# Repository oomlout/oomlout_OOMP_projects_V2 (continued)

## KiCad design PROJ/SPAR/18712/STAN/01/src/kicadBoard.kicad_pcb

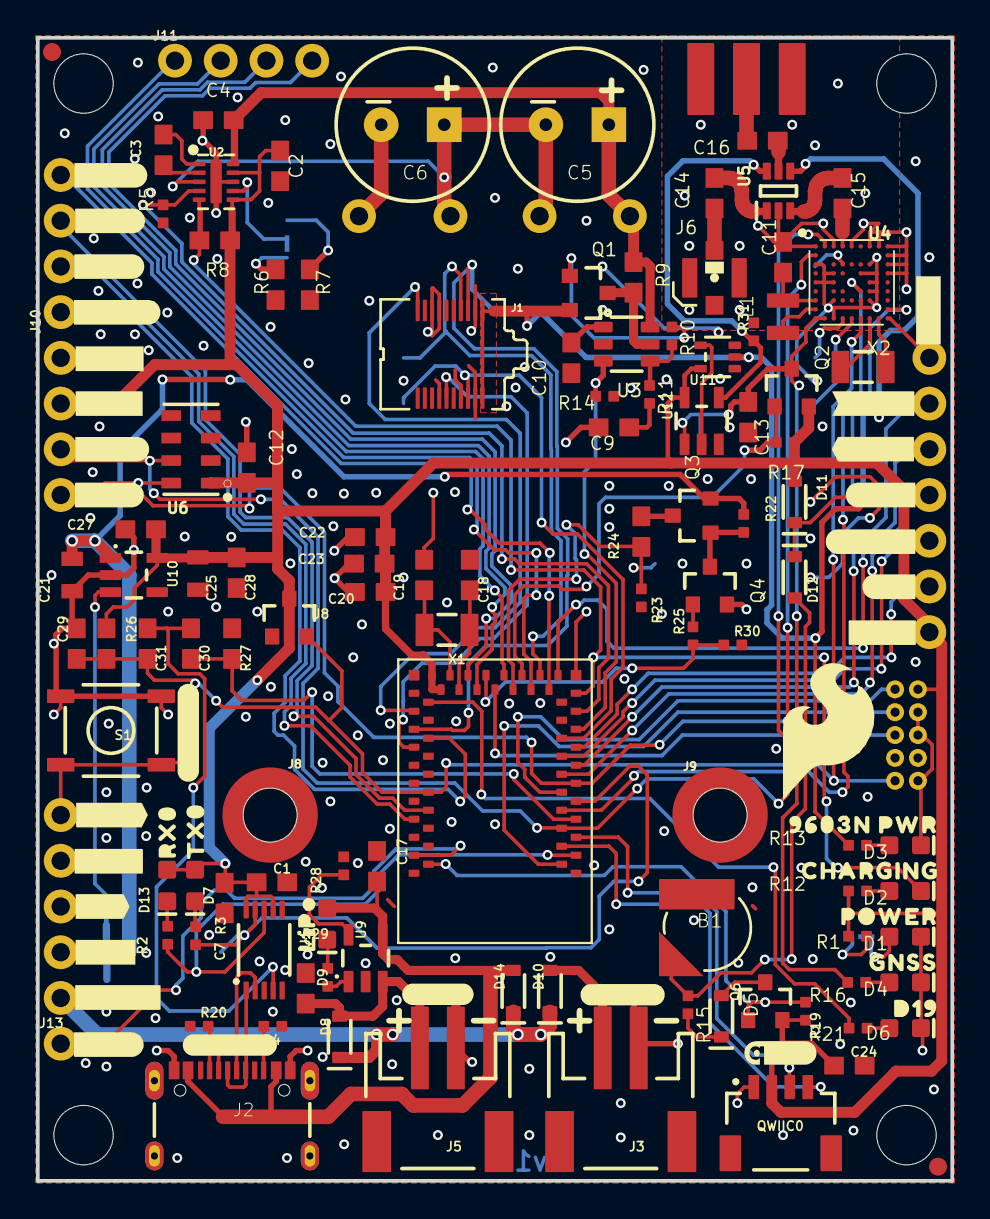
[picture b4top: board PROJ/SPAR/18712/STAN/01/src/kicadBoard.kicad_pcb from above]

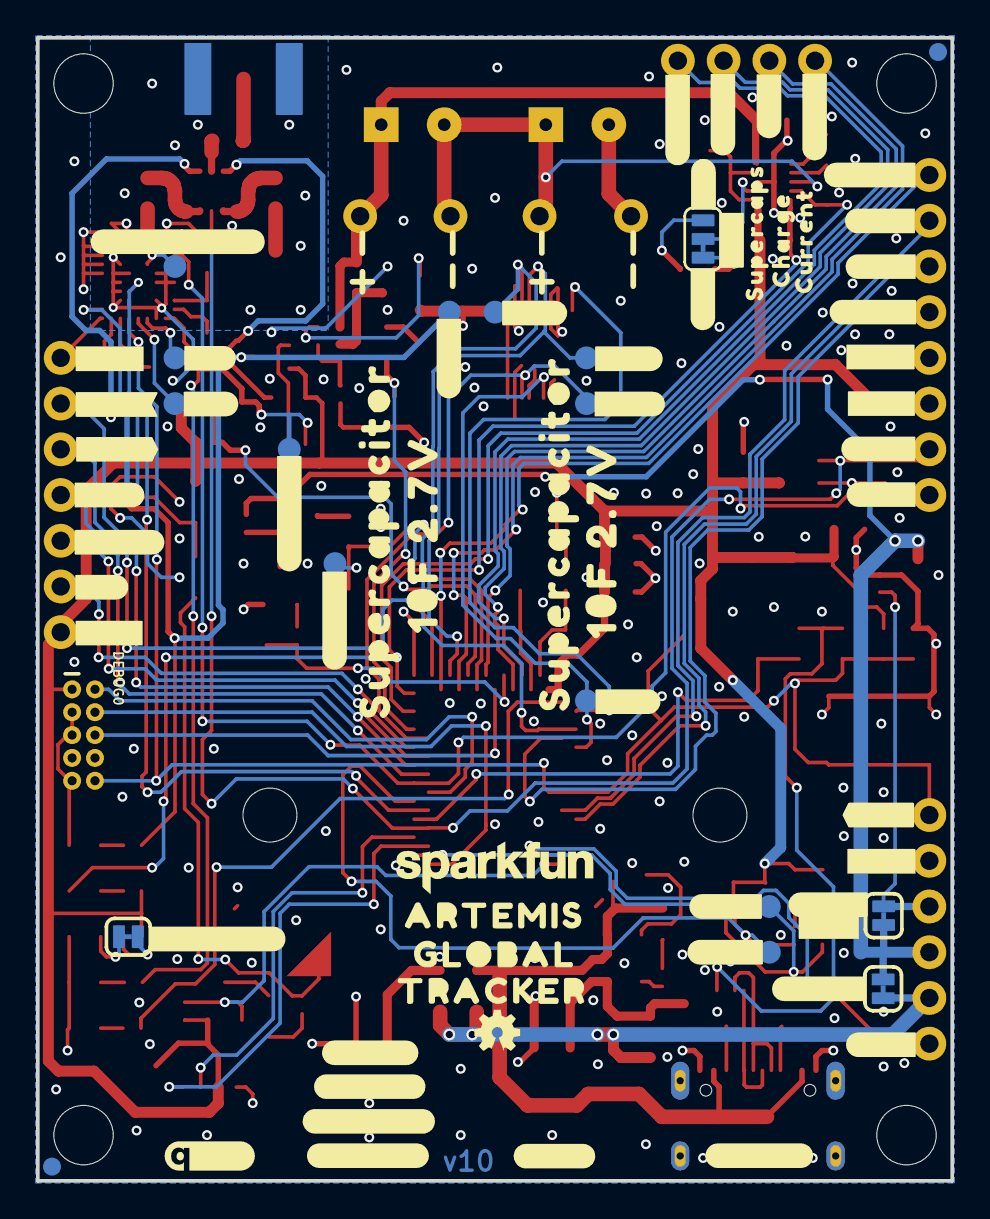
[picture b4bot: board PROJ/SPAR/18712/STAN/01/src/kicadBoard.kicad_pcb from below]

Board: 2 copper layers, 50.8 x 63.5 mm, 240 parts (79 on the bottom side), 101 nets.

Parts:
!RESET0: 1X01_NO_SILK
B1: ML414H_IV01E_BATTERY; ML414H_IV01E
C1, C9: 10nF; 0603
C2: 2.2uF; 0603
C3, C10, C23, C24, C27: 1.0uF; 0603
C4, C12: 0.22uF; 0603
C5, C6: 1F 2.7V; CPOL-RADIAL-1F-2.7V
C7, C13, C20, C28, C30, C31: 0.1uF; 0603
C8, C11, C17: 4.7uF; 0603
C14, C15, C16: 100pF; 0603
C18, C19: 15pF; 0603
C21, C25: 22uF; 0805
C22: 10uF; 0603
C29: 1nF; 0603
D1, D7: GREEN; LED-0603
D2, D9, D13: Yellow; LED-0603
D3: RED; LED-0603
D4: BLUE; LED-0603
D5, D8, D10, D11, D12, D14: 0.5A/40V/420mV; SOD-323
D6: WHITE; LED-0603
D17, D41: PAD.03X.05
DEBUG0: CORTEX_DEBUG; 2X5-PTH-1.27MM-NO_SILK
EN0: 1X01_NO_SILK
FRAME3: FRAME-LETTERNO_PACKAGE; DUMMY
FRAME5: FRAME-LEDGER; CREATIVE_COMMONS
GND0: 1X01_NO_SILK
GPS_RX0: TEST-POINT3X5; PAD.03X.05
GPS_TX0: TEST-POINT3X5; PAD.03X.05
I2C0: PTH; 1X04_NO_SILK
J1: IRIDIUM_9603N
J2: USB-C; USB-C-16P-2LAYER-PADS
J3, J5: JST-2-SMD
J4: 1X02_NO_SILK
J6: U.FL
J7: ANTENNA-GROUNDEDEDGE_SMA; SMA-EDGE
J8, J9: STAND-OFF-REFLOW-M2.0_6.0MM_TALL; STAND-OFF-REFLOW-M2.0
J10, J11: 1X04_NO_SILK
J13: 1X01_NO_SILK
JP1: JUMPER-SMT_3_1-NC_TRACE_SILK; SMT-JUMPER_3_1-NC_TRACE_SILK
JP2: JUMPER-SMT_2_NC_TRACE_SILK; SMT-JUMPER_2_NC_TRACE_SILK
JP7, JP8, JP13, JP14: FIDUCIAL1X2; FIDUCIAL-1X2
JP9, JP10, JP11, JP12: STAND-OFF
L1: 2.2uH; 0806
LOGO1: SFE_LOGO_NAME.1_INCH; SFE_LOGO_NAME_.1
LOGO2: SFE_LOGO_FLAME.3_INCH; SFE_LOGO_FLAME_.3
LOGO4: OSHW-LOGOMINI; OSHW-LOGO-MINI
MEAS0: JUMPER-SMT_2_NC_TRACE_SILK; SMT-JUMPER_2_NC_TRACE_SILK
Q1: 5.8A/30V/35mΩ; SOT23-3
Q2, Q3, Q6: 20V/4.2A/52mΩ/1.4W; SOT23-3
Q4: 600mA/40V; SOT23-3
QWIIC0: QWIIC_RA; JST04_1MM_RA
R1: 330; 0402-TIGHT
R2, R3, R12, R16, R21, R25, R29: 1k; 0402-TIGHT
R4, R20: 5.1k; 0402-TIGHT
R5, R14, R17, R19, R22, R23, R30: 10K; 0402-TIGHT
R6: 12k; 0603
R7: 30.1k; 0603
R8, R26: 100k; 0603
R9: 0.015ohm; 0603
R10, R11: 100; 0402-TIGHT
R13, R28: 2.0K; 0402-TIGHT
R15: 3.3K; 0402-TIGHT
R24: 20k; 0603
R27: 220k; 0603
R31: 20k; 0402-TIGHT
RX0, RX1: TEST-POINT3X5; PAD.03X.05
S1: RESET; TACTILE_SWITCH_SMD_5.2MM
SAFEBOOT0: TEST-POINT3X5; PAD.03X.05
SC1+0, SC1-0, SC2+0, SC2-0: 1X01_NO_SILK
SPI0: 1X07_NO_SILK
TX0, TX1: TEST-POINT3X5; PAD.03X.05
U1: CH340E_MSOP10; MSOP10
U2: LTC3225EDDB; DFN300X200-10L
U3: ADM4210_1TSOT6; TSOT6
U4: u-blox_ZOE_M8Q-0-10; UBLOX_ZOE_M8-0-10
U5: AS179-92LF; SOT65P220X100-6N
U6: MS8607-02BA01
U7: ARTEMIS_MODULESMD; ARTEMIS_FP
U8: V_SUPERVISOR_BD48K24G_2.4V; SOT23-3
U9: MCP73831; SOT23-5
U10: 3.3V; SOT23-5
U11: 74LVC1G04SE; SOT353
U12: 74LVC1G08W5-7; SOT23-5
U$1, U$13: SUPERCAPACITOR151
U$2: #SCK#199608
U$3, U$43: #3V3#0
U$4: #SDA#0
U$5: #USB#C#0
U$6: #SCL#0
U$7: #VIN#158
U$8: #3V3SW#0
U$9: CHARGING9604
U$10: #COPI#9694
U$11: QWIIC_4MM
U$12: LIPO5
U$14, U$15: 10F_2#7V152
U$16: RX06
U$17, U$70: #3V3#153
U$18: TX07
U$19: #AD35#199609
U$20, U$36: #GND#0
U$21: #SDA#153
U$22: #SCL#154
U$24: #AD31#7
U$25: QWIIC_5MM
U$26: #_RST##156
U$27: #EN#157
U$28: #VIN#3#0
U$29: #AD35#0
U$30: ARTEMIS0
U$31: SUPERCAPS6
U$32: #D17#0
U$33: #SAFEBOOT#0
U$34: #TX0#0
U$35: #TX1#0
U$37: #RX#0
U$38: #RX1#0
U$39: #TX#0
U$40: #5#3V#0
U$41: #D41#0
U$42: #RX0#0
U$44: #RESET#162
U$45: #SOLAR#165
U$46: #LIPO#164
U$47: #MEAS#0
U$48: #3V3_#0
U$50: #D4#36
U$51: GLOBAL0
U$52: TRACKER0
U$53: #LIPO#0
U$54: #_EN_#0
U$55: #SOLAR#0
U$56: #USB#C#161
U$57: #3_X_AA#0
U$58: #VBUS#159
U$59: #AD32#152
U$60: #SCK#9696
U$61: #PWR_LED#0
U$63: #D4#5
U$64: #CIPO#2
U$65: #3_X_AAA#0
U$66: #6V_MAX#0
U$67: CHARGE8
U$69: CURRENT9
U$71: #D42#32
U$72: #D37#152
U$73: #D43#43
U$74: #150#61
U$75: #COPI#5
U$76, U$77, U$78: #GND#152
U$79: #A32#44
U$80: #MA#45
U$81: #60#46
U$82: #D43#151
U$83: #D42#151
U$84: #AD31#151
U$85: #AD12#151
U$86: #D15#151
U$87: #AD11#151
U$88: #AD29#151
U$89: #CIPO#151
U$90: #D37#0
U$91: #GND#38
U$92: ##RST##39
U$93: 9603N_PWR40
U$94: POWER9605
U$95: GNSS9606
U$96: D199607
UNK3V3EN0: JUMPER-SMT_2_NC_TRACE_SILK; SMT-JUMPER_2_NC_TRACE_SILK
UNK3V3SW0: PAD.03X.05
UNK5V3: TEST-POINT3X5; PAD.03X.05
VIN/3: TEST-POINT3X5; PAD.03X.05
X1, X2: 32.768kHz; CRYSTAL-SMD-3.2X1.5MM

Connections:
3.3V: C1.1, C2.1, C7.1, C12.1, C20.2, C22.1, C23.1, C24.1, C25.1, C27.1, C28.1, D7.A, D11.A, D13.A, DEBUG0.1, I2C0.2, Q2.2, Q6.2, QWIIC0.2, R1.2, R8.2, R12.2, R17.2, R19.2, R26.2, SPI0.7, U1.7, U1.10, U2.6, U2.9, U6.1, U7.VDD@36, U7.VDD@37, U8.3, U10.5, U11.5, U12.5
3V3SW: C13.1, Q2.3, R16.2, U4.24, U4.25, U12.1, UNK3V3SW0.1
ANTENNA: C16.1, J7.SIG
ARTEMIS_AD11: J11.3, U7.~AD11
ARTEMIS_AD12: J11.1, U7.~AD12
ARTEMIS_AD29: J11.4, U7.~AD29
ARTEMIS_AD31: J10.1, U7.~AD31
ARTEMIS_AD32: J10.4, U7.~AD32
ARTEMIS_BOOT: C30.2, R27.2, U7.BOOT
ARTEMIS_D4: SPI0.6, U7.~D4
ARTEMIS_D5_SCK: SPI0.4, U7.~D5
ARTEMIS_D6_MISO: SPI0.3, U7.~D6
ARTEMIS_D7_MOSI: SPI0.2, U7.D7
ARTEMIS_D8_SCL: I2C0.4, U4.32, U6.8, U7.D8
ARTEMIS_D9_SDA: I2C0.3, U4.2, U6.7, U7.D9
ARTEMIS_D10: U4.50, U7.D10
ARTEMIS_D13: R23.1, R24.2, U7.~AD13, VIN/3.1
ARTEMIS_D15: J11.2, U7.D15
ARTEMIS_D17: D17.1, J1.5, U7.D17
ARTEMIS_D18: J1.19, U7.~D18
ARTEMIS_D19: R21.2, U7.~D19
ARTEMIS_D22: R14.1, U3.3, U7.~D22
ARTEMIS_D24: J1.6, TX1.1, U7.~D24
ARTEMIS_D25: J1.7, RX1.1, U7.~D25
ARTEMIS_D26: Q2.1, R17.1, U7.~D26
ARTEMIS_D27: R5.2, U2.4, U7.~D27
ARTEMIS_D28: D2.C, R8.1, U2.5, U7.~D28
ARTEMIS_D33: DEBUG0.6, U7.~AD33/SWO
ARTEMIS_D34: R25.1, R30.1, U7.AD34
ARTEMIS_D35: SPI0.5, U7.~AD35
ARTEMIS_D37: J13.1, U7.~D37
ARTEMIS_D39_SCL4: QWIIC0.4, U7.~D39
ARTEMIS_D40_SDA4: QWIIC0.3, U7.D40
ARTEMIS_D41: D41.1, J1.12, U7.D41
ARTEMIS_D42: J10.2, U7.~D42
ARTEMIS_D43: J10.3, U7.~D43
ARTEMIS_D44: Q6.1, R19.1, U7.~D44
ARTEMIS_RX0: R2.1, RX0.1, U1.8, U7.RXI-0
ARTEMIS_SWDCK: DEBUG0.4, U7.SWDCK
ARTEMIS_SWDIO: DEBUG0.2, U7.SWDIO
ARTEMIS_TX0: R3.1, TX0.1, U1.9, U7.TXO-0
ARTEMIS_~RESET: !RESET0.1, C29.1, C31.2, DEBUG0.10, R26.1, S1.3, S1.4, U4.20, U7.~RST, U8.2
ARTEMIS_~RTS: C30.1, C31.1, U1.4
CC3: J2.B5, R4.2
CC4: J2.A5, R20.2
D+2: J2.A6, J2.B6, U1.1
D-2: J2.A7, J2.B7, U1.2
EXT_PWR: J1.1, J1.2, Q1.2, R13.2, U5.4, U11.2, UNK5V3.1
GND: B1.-, C1.2, C2.2, C4.2, C6.-, C7.2, C8.2, C9.2, C10.2, C11.2, C12.2, C13.2, C17.2, C18.1, C19.1, C20.1, C21.2, C22.2, C23.2, C24.2, C25.2, C27.2, C28.2, C29.2, D1.C, D3.C, D4.C, D6.C, DEBUG0.3, DEBUG0.5, DEBUG0.9, GND0.1, I2C0.1, J1.3, J1.4, J1.8, J1.13, J1.14, J1.15, J1.18, J2.GND, J2.GND2, J3.1, J5.1, J6.1, J6.2, J7.GND@0, J7.GND@1, J7.GND@2, J7.GND@3, J8.1, J9.1, Q4.2, QWIIC0.1, R4.1, R5.1, R6.1, R7.2, R14.2, R20.1, R23.2, R27.1, R28.1, R30.2, R31.2, S1.1, S1.2, SC2-0.1, SPI0.1, U1.3, U2.8, U2.11, U3.2, U4.1, U4.3, U4.5, U4.7, U4.8, U4.9, U4.10, U4.11, U4.12, U4.17, U4.23, U4.29, U4.31, U4.37, U4.38, U4.39, U4.40, U4.41, U4.44, U4.46, U4.47, U4.49, U5.2, U6.3, U7.GND@1, U7.GND@22, U7.GND@38, U7.GND@39, U7.GND@47, U7.GND@59, U8.1, U9.2, U10.2, U11.3, U12.3
GNSS: C15.2, U4.4
IRIDIUM: C14.2, J6.FEED
LTC3225_VOUT: C4.1, C5.+, R9.2, SC1+0.1, U2.10, U3.6
unnamed: C5.-, C6.+, SC1-0.1, SC2+0.1, U2.3
unnamed: JP1.3, R6.2
unnamed: JP2.2, R1.1
unnamed: JP1.1, R7.1
unnamed: D2.A, R12.1
unnamed: D3.A, R13.1
unnamed: D5.A, Q6.3
unnamed: Q1.3, R9.1, U3.5
unnamed: C3.2, U2.2
unnamed: C3.1, U2.1
unnamed: JP1.2, U2.7
unnamed: Q1.1, R10.1
unnamed: R10.2, R11.1, U3.4
unnamed: C9.1, R11.2
unnamed: C10.1, U3.1
unnamed: L1.2, U4.26
unnamed: C11.1, L1.1, U4.27
unnamed: U4.18, X2.P$2
unnamed: U4.19, X2.P$1
unnamed: D5.C, R15.2
unnamed: D4.A, R16.1
unnamed: D13.C, R2.2
unnamed: D1.A, JP2.1
unnamed: D11.C, D12.C, U4.16
unnamed: SAFEBOOT0.1, U4.34
unnamed: GPS_RX0.1, U4.22
unnamed: GPS_TX0.1, U4.21
unnamed: C14.1, U5.1
unnamed: C15.1, U5.3
unnamed: C16.2, U5.5
unnamed: R31.1, U5.6, U12.4
unnamed: D7.C, R3.2
unnamed: U11.4, U12.2
unnamed: D6.A, R21.1
unnamed: EN0.1, U10.3, UNK3V3EN0.2
unnamed: Q3.1, Q4.3, R22.1
unnamed: R28.2, U9.5
unnamed: D9.C, R29.2
unnamed: R29.1, U9.1
unnamed: Q3.3, R24.1
unnamed: Q4.1, R25.2
VBUS: D8.C, D10.C, D14.C, J4.2, MEAS0.1
VIN: C21.1, J4.1, MEAS0.2, Q3.2, R22.2, U10.1, UNK3V3EN0.1
V_AAA: D10.A, J3.2
V_BATT: C8.1, D8.A, J5.2, U9.3
V_BCKP: B1.+, D12.A, R15.1
V_USB: C17.1, D9.A, D14.A, J2.VBUS1, J2.VBUS2, U9.4
XTALI: C19.2, U7.XI, X1.P$1
XTALO: C18.2, U7.XO, X1.P$2

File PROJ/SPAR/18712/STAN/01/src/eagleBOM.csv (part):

"Part";"Value";"Device";"Package";"Description";"DESIGNER";"PROD_ID";"REV";"SF_ID";"VALUE";"VERSION";"VOLTAGE";
"!RESET";"";"CONN_01PTH_NO_SILK_YES_STOP";"1X01_NO_SILK";"Single connection point. Often used as Generic Header-pin footprint for 0.1 inch spaced/style header connections";"";"";"";"";"";"";"";
"3V3EN";"JUMPER-SMT_2_NC_TRACE_SILK";"JUMPER-SMT_2_NC_TRACE_SILK";"SMT-JUMPER_2_NC_TRACE_SILK";"Normally closed trace jumper";"";"";"";"";"";"";"";
"3V3SW";"";"TEST-POINT3X5";"PAD.03X.05";"SparkFun Test Points";"";"";"";"";"";"";"";
"5V3";"TEST-POINT3X5";"TEST-POINT3X5";"PAD.03X.05";"SparkFun Test Points";"";"";"";"";"";"";"";
"B1";"ML414H_IV01E_BATTERY";"ML414H_IV01E_BATTERY";"ML414H_IV01E";"SEIKO ML414H-IV01E Reflowable Lithium Battery";"";"BATT-14267";"";"";"";"";"";
"C1";"10nF";"10NF-0603-50V-10%";"0603";"0.01uF/10nF/10,000pF ceramic capacitors";"";"CAP-00867";"";"";"10nF";"";"";
"C2";"2.2uF";"2.2UF-0603-10V-20%";"0603";"2.2µF ceramic capacitors";"";"CAP-07888";"";"";"2.2uF";"";"";
"C3";"1.0uF";"1.0UF-0603-16V-10%-X7R";"0603";"1µF ceramic capacitors";"";"CAP-13930";"";"";"1.0uF";"";"";
"C4";"0.22uF";"0.22UF-0603-25V-10%";"0603";"0.22µF ceramic capacitors";"";"CAP-07822";"";"";"0.22uF";"";"";
"C5";"1F 2.7V";"1F-2.7V(PTH)CPOL-RADIAL-1H-2.7V";"CPOL-RADIAL-1F-2.7V";"1F 2.7V SuperCapacitor CAP-14696";"";"CAP-14696";"";"";"";"";"";
"C6";"1F 2.7V";"1F-2.7V(PTH)CPOL-RADIAL-1H-2.7V";"CPOL-RADIAL-1F-2.7V";"1F 2.7V SuperCapacitor CAP-14696";"";"CAP-14696";"";"";"";"";"";
"C7";"0.1uF";"0.1UF-0603-25V-5%";"0603";"0.1µF ceramic capacitors";"";"CAP-08604";"";"";"0.1uF";"";"";
"C8";"4.7uF";"4.7UF-0603-6.3V-(10%)";"0603";"4.7µF ceramic capacitors";"";"CAP-08280";"";"";"4.7uF";"";"";
"C9";"10nF";"10NF-0603-50V-10%";"0603";"0.01uF/10nF/10,000pF ceramic capacitors";"";"CAP-00867";"";"";"10nF";"";"";
"C10";"1.0uF";"1.0UF-0603-16V-10%-X7R";"0603";"1µF ceramic capacitors";"";"CAP-13930";"";"";"1.0uF";"";"";
"C11";"4.7uF";"4.7UF-0603-6.3V-(10%)";"0603";"4.7µF ceramic capacitors";"";"CAP-08280";"";"";"4.7uF";"";"";
"C12";"0.22uF";"0.22UF-0603-25V-10%";"0603";"0.22µF ceramic capacitors";"";"CAP-07822";"";"";"0.22uF";"";"";
"C13";"0.1uF";"0.1UF-0603-25V-5%";"0603";"0.1µF ceramic capacitors";"";"CAP-08604";"";"";"0.1uF";"";"";
"C14";"100pF";"100PF-0603-50V-5%";"0603";"100pF/0.1nF ceramic capacitors";"";"CAP-07883";"";"";"100pF";"";"";
"C15";"100pF";"100PF-0603-50V-5%";"0603";"100pF/0.1nF ceramic capacitors";"";"CAP-07883";"";"";"100pF";"";"";
"C16";"100pF";"100PF-0603-50V-5%";"0603";"100pF/0.1nF ceramic capacitors";"";"CAP-07883";"";"";"100pF";"";"";
"C17";"4.7uF";"4.7UF-0603-6.3V-(10%)";"0603";"4.7µF ceramic capacitors";"";"CAP-08280";"";"";"4.7uF";"";"";
"C18";"15pF";"15PF-0603-50V-5%";"0603";"15pF ceramic capacitors";"";"CAP-07881";"";"";"15pF";"";"";
"C19";"15pF";"15PF-0603-50V-5%";"0603";"15pF ceramic capacitors";"";"CAP-07881";"";"";"15pF";"";"";
"C20";"0.1uF";"0.1UF-0603-25V-5%";"0603";"0.1µF ceramic capacitors";"";"CAP-08604";"";"";"0.1uF";"";"";
"C21";"22uF";"22UF-0805-16V-20%";"0805";"22µF ceramic capacitors";"";"CAP-14260";"";"";"22uF";"";"";
"C22";"10uF";"10UF-0603-6.3V-20%";"0603";"10.0µF ceramic capacitors";"";"CAP-11015";"";"";"10uF";"";"";
"C23";"1.0uF";"1.0UF-0603-16V-10%-X7R";"0603";"1µF ceramic capacitors";"";"CAP-13930";"";"";"1.0uF";"";"";
"C24";"1.0uF";"1.0UF-0603-16V-10%-X7R";"0603";"1µF ceramic capacitors";"";"CAP-13930";"";"";"1.0uF";"";"";
"C25";"22uF";"22UF-0805-16V-20%";"0805";"22µF ceramic capacitors";"";"CAP-14260";"";"";"22uF";"";"";
"C27";"1.0uF";"1.0UF-0603-16V-10%-X7R";"0603";"1µF ceramic capacitors";"";"CAP-13930";"";"";"1.0uF";"";"";
"C28";"0.1uF";"0.1UF-0603-25V-5%";"0603";"0.1µF ceramic capacitors";"";"CAP-08604";"";"";"0.1uF";"";"";
"C29";"1nF";"1.0NF/1000PF-0603-50V-10%";"0603";"1nF/1,000pF ceramic capacitors";"";"CAP-07886";"";"";"1nF";"";"";
"C30";"0.1uF";"0.1UF-0603-25V-5%";"0603";"0.1µF ceramic capacitors";"";"CAP-08604";"";"";"0.1uF";"";"";
"C31";"0.1uF";"0.1UF-0603-25V-5%";"0603";"0.1µF ceramic capacitors";"";"CAP-08604";"";"";"0.1uF";"";"";
"D1";"GREEN";"LED-GREEN0603";"LED-0603";"Green SMD LED";"";"DIO-00821";"";"";"GREEN";"";"";
"D2";"Yellow";"LED-YELLOW0603";"LED-0603";"Yellow SMD LED";"";"DIO-09003";"";"";"Yellow";"";"";
"D3";"RED";"LED-RED0603";"LED-0603";"Red SMD LED";"";"DIO-00819";"";"";"RED";"";"";
"D4";"BLUE";"LED-BLUE0603";"LED-0603";"Blue SMD LED";"";"DIO-08575";"";"";"BLUE";"";"";
"D5";"0.5A/40V/420mV";"DIODE-SCHOTTKY-PMEG4005EJ";"SOD-323";"Schottky diode";"";"DIO-10955";"";"";"0.5A/40V/420mV";"";"";
"D6";"WHITE";"LED-WHITE0603";"LED-0603";"White SMD LED";"";"DIO-09004";"";"";"WHITE";"";"";
"D7";"GREEN";"LED-GREEN0603";"LED-0603";"Green SMD LED";"";"DIO-00821";"";"";"GREEN";"";"";
"D8";"0.5A/40V/420mV";"DIODE-SCHOTTKY-PMEG4005EJ";"SOD-323";"Schottky diode";"";"DIO-10955";"";"";"0.5A/40V/420mV";"";"";
"D9";"Yellow";"LED-YELLOW0603";"LED-0603";"Yellow SMD LED";"";"DIO-09003";"";"";"Yellow";"";"";
"D10";"0.5A/40V/420mV";"DIODE-SCHOTTKY-PMEG4005EJ";"SOD-323";"Schottky diode";"";"DIO-10955";"";"";"0.5A/40V/420mV";"";"";
"D11";"0.5A/40V/420mV";"DIODE-SCHOTTKY-PMEG4005EJ";"SOD-323";"Schottky diode";"";"DIO-10955";"";"";"0.5A/40V/420mV";"";"";
"D12";"0.5A/40V/420mV";"DIODE-SCHOTTKY-PMEG4005EJ";"SOD-323";"Schottky diode";"";"DIO-10955";"";"";"0.5A/40V/420mV";"";"";
"D13";"Yellow";"LED-YELLOW0603";"LED-0603";"Yellow SMD LED";"";"DIO-09003";"";"";"Yellow";"";"";
"D14";"0.5A/40V/420mV";"DIODE-SCHOTTKY-PMEG4005EJ";"SOD-323";"Schottky diode";"";"DIO-10955";"";"";"0.5A/40V/420mV";"";"";
"D17";"";"TEST-POINT3X5";"PAD.03X.05";"SparkFun Test Points";"";"";"";"";"";"";"";
"D41";"";"TEST-POINT3X5";"PAD.03X.05";"SparkFun Test Points";"";"";"";"";"";"";"";
"DEBUG";"CORTEX_DEBUG";"CORTEX_JTAG_DEBUG_MINIMUM_PTH_NS";"2X5-PTH-1.27MM-NO_SILK";"Cortex Debug Connector - 10 pin";"";"";"";"";"";"";"";
"EN";"";"CONN_01PTH_NO_SILK_YES_STOP";"1X01_NO_SILK";"Single connection point. Often used as Generic Header-pin footprint for 0.1 inch spaced/style header connections";"";"";"";"";"";"";"";
"FRAME3";"FRAME-LETTERNO_PACKAGE";"FRAME-LETTERNO_PACKAGE";"DUMMY";"Schematic Frame - Letter";"Nobody";"";"v10";"";"";"v10";"";
"FRAME5";"FRAME-LEDGER";"FRAME-LEDGER";"CREATIVE_COMMONS";"Schematic Frame - Ledger";"";"";"v10";"";"";"";"";
"GND";"";"CONN_01PTH_NO_SILK_YES_STOP";"1X01_NO_SILK";"Single connection point. Often used as Generic Header-pin footprint for 0.1 inch spaced/style header connections";"";"";"";"";"";"";"";
"GPS_RX";"TEST-POINT3X5";"TEST-POINT3X5";"PAD.03X.05";"SparkFun Test Points";"";"";"";"";"";"";"";
"GPS_TX";"TEST-POINT3X5";"TEST-POINT3X5";"PAD.03X.05";"SparkFun Test Points";"";"";"";"";"";"";"";
"I2C";"PTH";"I2C_STANDARD_NO_SILK";"1X04_NO_SILK";"SparkFun I2C Standard Pinout Header";"";"";"";"";"";"";"";
"J1";"IRIDIUM_9603N";"IRIDIUM_9603N";"IRIDIUM_9603N";"Iridium 9603N Modem";"";"CONN-14689";"";"";"IRIDIUM_9603N";"";"";
"J2";"USB-C";"USB_C_2-LAYER_PADS";"USB-C-16P-2LAYER-PADS";"USB Type C 16Pin Connector";"";"CONN-14122";"";"";"";"";"";
"J3";"";"JST_2MM_MALE";"JST-2-SMD";"JST 2MM MALE RA CONNECTOR";"";"CONN-11443";"";"PRT-08612";"";"";"";
"J4";"";"CONN_021X02_NO_SILK";"1X02_NO_SILK";"Multi connection point. Often used as Generic Header-pin footprint for 0.1 inch spaced/style header connections";"";"";"";"";"";"";"";
"J5";"";"JST_2MM_MALE";"JST-2-SMD";"JST 2MM MALE RA CONNECTOR";"";"CONN-11443";"";"PRT-08612";"";"";"";
"J6";"U.FL";"U.FL2PIN";"U.FL";"SMD Antenna Connector - U.FL";"";"CONN-09193";"";"WRL-09144";"U.FL";"";"";
"J7";"ANTENNA-GROUNDEDEDGE_SMA";"ANTENNA-GROUNDEDEDGE_SMA";"SMA-EDGE";"Antenna w/ Ground Connection";"";"CONN-08289";"";"";"";"";"";
"J8";"STAND-OFF-REFLOW-M2.0_6.0MM_TALL";"STAND-OFF-REFLOW-M2.0_6.0MM_TALL";"STAND-OFF-REFLOW-M2.0";"Stand Off Reflow Compatible";"";"HW-14879";"";"";"";"";"";
"J9";"STAND-OFF-REFLOW-M2.0_6.0MM_TALL";"STAND-OFF-REFLOW-M2.0_6.0MM_TALL";"STAND-OFF-REFLOW-M2.0";"Stand Off Reflow Compatible";"";"HW-14879";"";"";"";"";"";
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
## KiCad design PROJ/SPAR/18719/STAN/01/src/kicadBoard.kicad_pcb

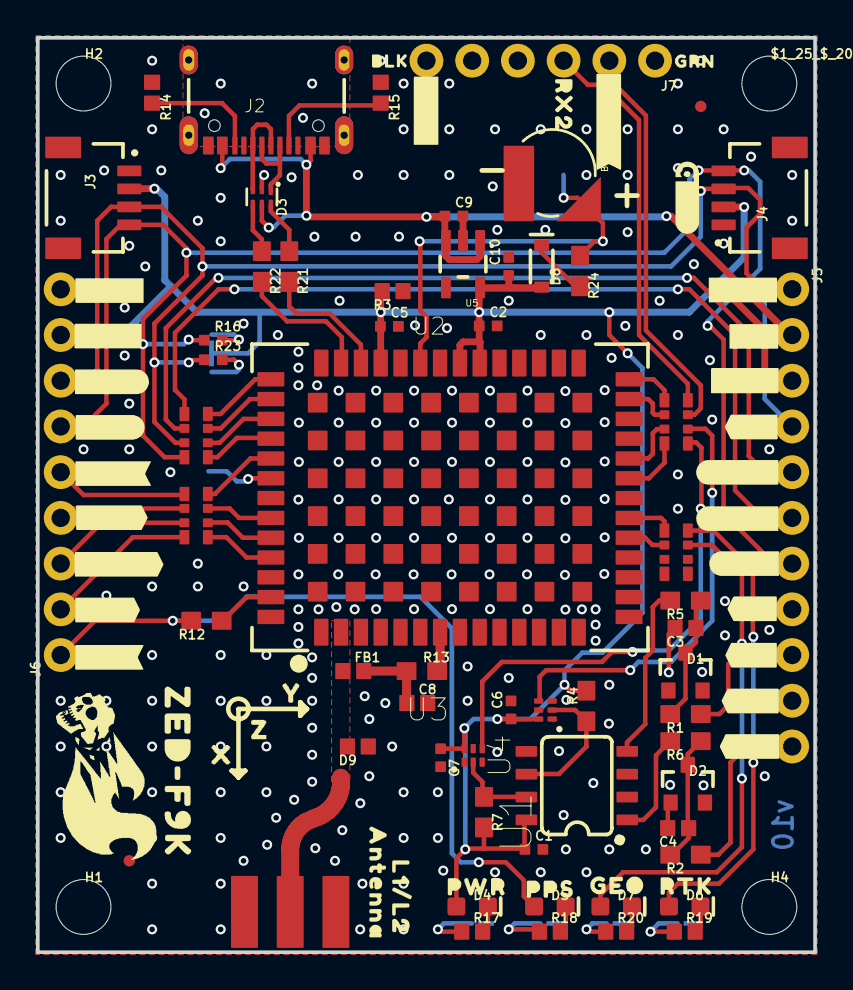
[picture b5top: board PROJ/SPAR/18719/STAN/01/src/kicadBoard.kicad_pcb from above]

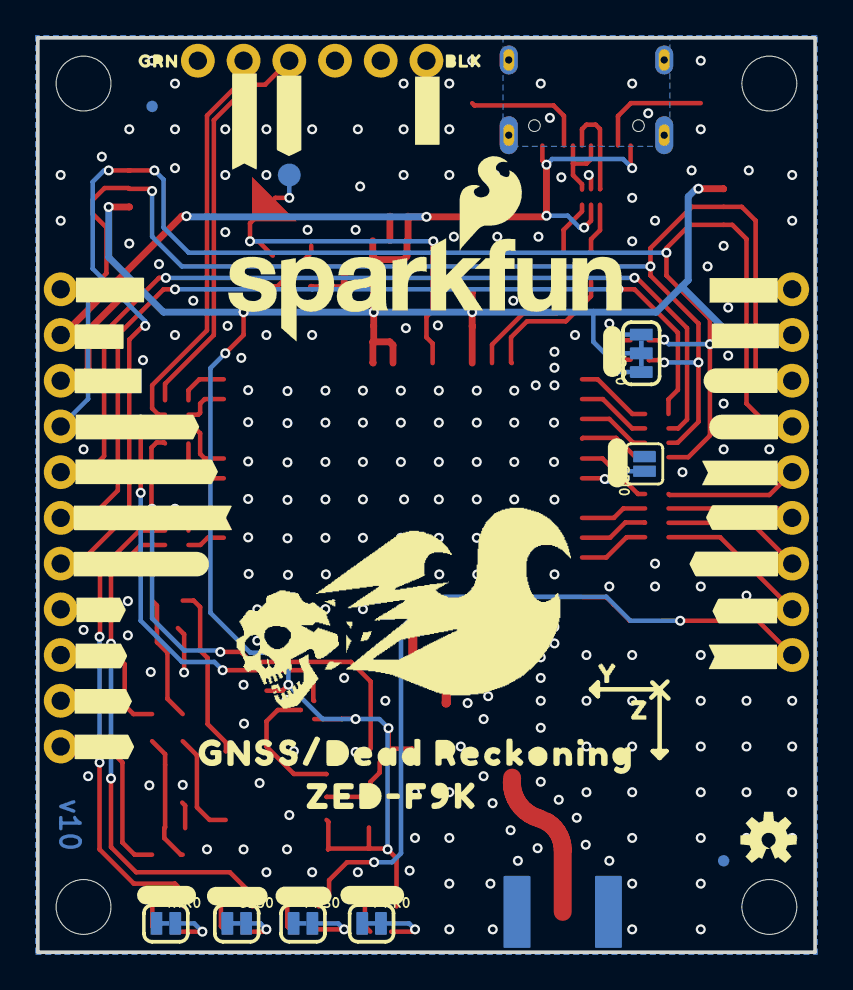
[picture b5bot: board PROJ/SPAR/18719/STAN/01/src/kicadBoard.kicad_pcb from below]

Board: 2 copper layers, 43.2 x 50.8 mm, 149 parts (47 on the bottom side), 66 nets.

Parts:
$1_25_$_2020-03-30_22-52-05: STAND-OFFTIGHT; STAND-OFF-TIGHT
BT1: ML414H_IV01E_BATTERY; ML414H_IV01E
C1, C5, C6, C7: 0.1uF; 0402-TIGHT
C2, C9, C10: 1.0uF; 0402-TIGHT
C3, C4: 1nF; 0402
C8: 47pF; 0402
D1, D2: 15V; SOT23-3
D3: PRTR5V0U2F; SOT886
D4: RED; LED-0603
D5, D6, D7: BLUE; LED-0603
D8: 0.5A/40V/420mV; SOD-323
D9: PESD0402-0402; 0402
E1: ANTENNA-SMA-GROUNDEDEDGE_SMA; SMA-EDGE
FB1: 120Ω; 0402
FD1, FD2, FD3, FD4: FIDUCIALUFIDUCIAL; FIDUCIAL-MICRO
FRAME1: FRAME-LEDGER; CREATIVE_COMMONS
GEO0: JUMPER-SMT_2_NC_TRACE_SILK; SMT-JUMPER_2_NC_TRACE_SILK
H1, H2, H4: STAND-OFFTIGHT; STAND-OFF-TIGHT
I2C0: JUMPER-SMT_3_2-NC_TRACE_SILK; SMT-JUMPER_3_2-NC_TRACE_SILK
J2: USB-C-16P-2LAYER-PADS
J3, J4: QWIIC_RIGHT_ANGLE; JST04_1MM_RA
J5: 1X11_NO_SILK
J6: 1X09_NO_SILK
J7: 1X06_NO_SILK
LOGO1: OSHW-LOGOS; OSHW-LOGO-S
LOGO2: QWIIC_LOGO_4MM; QWIIC_4MM
LOGO3: SFE_LOGO_NAME_FLAME.2_INCH; SFE_LOGO_NAME_FLAME_.2
PPS0: JUMPER-SMT_2_NC_TRACE_SILK; SMT-JUMPER_2_NC_TRACE_SILK
PWR0: JUMPER-SMT_2_NC_TRACE_SILK; SMT-JUMPER_2_NC_TRACE_SILK
R1, R2, R24: 3.3k; 0603
R3: 100K; 0402
R4, R7: 910; 0603
R5, R6: 470; 0603
R8, R9, R10, R11: 33; 1206_RA
R12, R13: 33; 0603
R14, R15: 5.1k; 0402
R16, R23: 4.7k; 0402-TIGHT
R17, R18, R19, R20: 1KOHM-0402-1/16W-1%; 0402
R21, R22: 27; 0603
RTK0: JUMPER-SMT_2_NC_TRACE_SILK; SMT-JUMPER_2_NC_TRACE_SILK
SPI0: JUMPER-SMT_2_NO_SILK; SMT-JUMPER_2_NO_SILK
TP1: TEST-POINT3X5; PAD.03X.05
U1: DUAL-OPTO_HCPL-073LSOIC-8; SO08
U2: U-BLOX_ZED_F9K; UBLOX_ZED_F9K
U3, U4: UHS_INVERTER_SCHMITT_TRIGGERSIP6; SIP6
U5: 3.3V; SOT23-5
U$1: PWR22
U$2: PPS21
U$3: GEO23
U$4: RTK24
U$5: #W##16
U$6: #W##15
U$7, U$14, U$22, U$37, U$55: #3V3#6
U$8: #D##13
U$9: #D##14
U$10: #SCK#12
U$11: #CIPO#10
U$12: #COPI#9
U$13: ##CS##11
U$15, U$24: #5V#1
U$16, U$17, U$25, U$36, U$44, U$58: #GND#0
U$18: #TXO2#20
U$19, U$20: DEAD#RECKONING#GPS#BOARD#SILK#FINAL#JPG
U$21: RX224
U$23: BLK225
U$26: GRN226
U$27: #SDA##CS##10
U$28: #RXI#COPI#8
U$30: #SCL#SCK#12
U$31: #D##6
U$32: X1
U$33: #D##7
U$34: #W##4
U$35: #W##5
U$38: #SDA#6
U$39: #SCL#7
U$40: #TXR#3
U$41: ##RST##16
U$42: ##SFBT##17
U$43: #INT#8
U$45: #PPS#0
U$46: #RTK#25
U$47: #GEO#24
U$48: #PPS#21
U$49: L1#L2229
U$50, U$52: Y2
U$51: #PWR#23
U$53: #SPI#22
U$54: #I2C#23
U$56: #SDA#12
U$57, U$63: Z0
U$59: #RXI2#227
U$60: #TXO2#1
U$61: BLK227
U$62: ANTENNA229
U$64: GRN228
U$65: GNSS#DEAD_RECKONING230
U$66: #SCL#13
U$67: #TXR#19
U$68: ##RST##17
U$69: ##SFBT##18
U$70: #INT#14
U$71: #PPS#20
U$72, U$73: ZED#F9K230
U$74: #TXO#CIPO#9

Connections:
3.3V: C1.1, C2.1, C5.1, C6.1, C7.1, C10.1, D4.A, D8.A, I2C0.2, J3.2, J4.2, J5.3, J6.8, R3.2, R4.2, R7.2, U1.8, U2.P33, U2.P34, U2.P38, U3.P6, U4.P6, U5.5
DIR+: J5.9, R1.1
DIR_IN: R5.2, U1.4
DIR_INV: R4.1, U1.6, U4.P2
DIR_OUT: R10.P6, U4.P4
DMINUS: R21.2, U2.P39
DPLUS: R22.2, U2.P40
D_SEL: SPI0.1, U2.P47
GEOF_STAT: D7.A, R11.P7
GND: BT1.-, C1.2, C2.2, C3.2, C4.2, C5.2, C6.2, C7.2, C8.2, C9.2, C10.2, D1.1, D2.1, D3.2, D9.1, E1.GND@0, E1.GND@1, E1.GND@2, E1.GND@3, GEO0.1, J2.GND, J2.GND2, J3.1, J4.1, J5.1, J5.8, J5.10, J6.9, J7.6, PPS0.1, PWR0.1, R3.1, R14.1, R15.1, RTK0.1, SPI0.2, U1.2, U1.3, U1.5, U2.G1, U2.G2, U2.G3, U2.G4, U2.G5, U2.G6, U2.G7, U2.G8, U2.G9, U2.G10, U2.G11, U2.G12, U2.G13, U2.G14, U2.G15, U2.G16, U2.G17, U2.G18, U2.G19, U2.G20, U2.G21, U2.G22, U2.G23, U2.G24, U2.G25, U2.G26, U2.G27, U2.G28, U2.G29, U2.G30, U2.G31, U2.G32, U2.G33, U2.G34, U2.G35, U2.G36, U2.G37, U2.G38, U2.G39, U2.G40, U2.G41, U2.G42, U2.G43, U2.G44, U2.G45, U2.G46, U2.G47, U2.G48, U2.P1, U2.P3, U2.P12, U2.P14, U2.P32, U2.P37, U2.P41, U2.P48, U3.P3, U4.P3, U5.2
INT: J6.2, R8.P4
unnamed: I2C0.1, R23.2
unnamed: D8.C, R24.2
unnamed: I2C0.3, R16.2
unnamed: D4.C, R17.2
unnamed: C8.1, FB1.2, R13.1
unnamed: D3.3, J2.A6, J2.B6
unnamed: D3.1, J2.A7, J2.B7
unnamed: PWR0.2, R17.1
unnamed: D3.6, R21.1
unnamed: D3.4, R22.1
unnamed: R8.P7, U2.P49
unnamed: R8.P5, U2.P51
unnamed: J2.B5, R14.2
unnamed: J2.A5, R15.2
unnamed: R9.P6, U2.P44
unnamed: R9.P5, U2.P45
unnamed: R8.P8, U2.P46
unnamed: R9.P8, U2.P42
unnamed: R9.P7, U2.P43
unnamed: R10.P1, U2.P27
unnamed: R19.1, RTK0.2
unnamed: PPS0.2, R18.1
unnamed: D5.C, R18.2
unnamed: D6.C, R19.2
unnamed: R10.P2, U2.P26
unnamed: R11.P2, U2.P19
unnamed: R11.P1, U2.P20
unnamed: R12.1, U2.P53
unnamed: R8.P6, U2.P50
unnamed: R10.P4, U2.P22
unnamed: R10.P3, U2.P23
unnamed: GEO0.2, R20.1
unnamed: D7.C, R20.2
unnamed: C4.1, D2.3, R2.2, R6.1
unnamed: C3.1, D1.3, R1.2, R5.1
PPS: D5.A, J6.1, R12.2
RF_IN: D9.2, E1.SIG, FB1.1, U2.P2
RTK_STAT: D6.A, R11.P8
RXI2: J7.3, R10.P7
RXI/COPI: J5.5, R9.P2
SCL/CLK: J3.4, J4.4, J5.7, J6.6, R9.P4, R16.1
SDA/~CS: J3.3, J4.3, J5.4, J6.7, R9.P3, R23.1
SHIELD: J2.SHLD1, J2.SHLD2, J2.SHLD3, J2.SHLD4
TXO2: J7.2, R10.P8
TXO/CIPO: J5.6, R9.P1
TX_READY: J6.5, R8.P1
VIN: C9.1, D3.5, J2.VBUS1, J2.VBUS2, J5.2, U5.1, U5.3
V_BATT: BT1.+, R24.1, TP1.1, U2.P36
V_RF: R13.2, U2.P7
WT+: J5.11, R2.1
WT_IN: R6.2, U1.1
WT_INV: R7.1, U1.7, U3.P2
WT_OUT: R10.P5, U3.P4
~RESET: J6.4, R8.P2
~SAFEBOOT: J6.3, R8.P3

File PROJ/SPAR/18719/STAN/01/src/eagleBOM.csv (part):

"Part";"Value";"Device";"Package";"Description";"DESIGNER";"DIGIKEY_PART";"MFG_PART";"MOUSE_PART";"PROD_ID";"REV";"VALUE";
"$1_25_$_2020-03-30_22-52-05";"STAND-OFFTIGHT";"STAND-OFFTIGHT";"STAND-OFF-TIGHT";"Stand Off";"";"";"";"";"";"";"";
"BT1";"ML414H_IV01E_BATTERY";"ML414H_IV01E_BATTERY";"ML414H_IV01E";"SEIKO ML414H-IV01E Reflowable Lithium Battery";"";"";"";"";"BATT-14267";"";"";
"C1";"0.1uF";"0.1UF-0402T-6.3V-10%-X7R";"0402-TIGHT";"0.1µF ceramic capacitors";"";"";"";"";"CAP-14993";"";"0.1uF";
"C2";"1.0uF";"1.0UF-0402T-16V-10%";"0402-TIGHT";"1µF ceramic capacitors";"";"";"";"";"CAP-12417";"";"1.0uF";
"C3";"1nF";"1.0NF/1000PF-0402-25V-10%-X7R";"0402";"1nF/1,000pF ceramic capacitors";"";"";"";"";"CAP-15061";"";"1nF";
"C4";"1nF";"1.0NF/1000PF-0402-25V-10%-X7R";"0402";"1nF/1,000pF ceramic capacitors";"";"";"";"";"CAP-15061";"";"1nF";
"C5";"0.1uF";"0.1UF-0402T-6.3V-10%-X7R";"0402-TIGHT";"0.1µF ceramic capacitors";"";"";"";"";"CAP-14993";"";"0.1uF";
"C6";"0.1uF";"0.1UF-0402T-6.3V-10%-X7R";"0402-TIGHT";"0.1µF ceramic capacitors";"";"";"";"";"CAP-14993";"";"0.1uF";
"C7";"0.1uF";"0.1UF-0402T-6.3V-10%-X7R";"0402-TIGHT";"0.1µF ceramic capacitors";"";"";"";"";"CAP-14993";"";"0.1uF";
"C8";"47pF";"47PF-0402-25V-5%-X7R";"0402";"47pF ceramic capacitors";"";"";"";"";"CAP-15063";"";"47pF";
"C9";"1.0uF";"1.0UF-0402T-16V-10%";"0402-TIGHT";"1µF ceramic capacitors";"";"";"";"";"CAP-12417";"";"1.0uF";
"C10";"1.0uF";"1.0UF-0402T-16V-10%";"0402-TIGHT";"1µF ceramic capacitors";"";"";"";"";"CAP-12417";"";"1.0uF";
"D1";"15V";"DIODE-ZENER-BZX84C15LT3G";"SOT23-3";"Zener Diode";"";"";"";"";"DIO-15071";"";"15V";
"D2";"15V";"DIODE-ZENER-BZX84C15LT3G";"SOT23-3";"Zener Diode";"";"";"";"";"DIO-15071";"";"15V";
"D3";"PRTR5V0U2F";"PRTR5V0U2F";"SOT886";"A small ESD protection device. Most commonly used on USB D+/D- signals to protect large, expensive, or especially sensitive USB enabled devices.";"";"";"";"";"DIO-14084";"";"";
"D4";"RED";"LED-RED0603";"LED-0603";"Red SMD LED";"";"";"";"";"DIO-00819";"";"RED";
"D5";"BLUE";"LED-BLUE0603";"LED-0603";"Blue SMD LED";"";"";"";"";"DIO-08575";"";"BLUE";
"D6";"BLUE";"LED-BLUE0603";"LED-0603";"Blue SMD LED";"";"";"";"";"DIO-08575";"";"BLUE";
"D7";"BLUE";"LED-BLUE0603";"LED-0603";"Blue SMD LED";"";"";"";"";"DIO-08575";"";"BLUE";
"D8";"0.5A/40V/420mV";"DIODE-SCHOTTKY-PMEG4005EJ";"SOD-323";"Schottky diode";"";"";"";"";"DIO-10955";"";"0.5A/40V/420mV";
"D9";"PESD0402-0402";"PESD0402-0402";"0402";"ESD protection diode";"";"PESD0402-140CT-ND";"";"650-PESD0402-140";"DIO-15359";"";"";
"E1";"ANTENNA-SMA-GROUNDEDEDGE_SMA";"ANTENNA-SMA-GROUNDEDEDGE_SMA";"SMA-EDGE";"SMA Antenna Connector w/ Ground";"";"";"";"";"CONN-08289";"";"";
"FB1";"120Ω";"FERRITE_BEAD-120_OHM-0402";"0402";"Ferrite Bead (blocks, cores, rings, chokes, etc.)";"";"";"BLM15HB121SN1D";"";"NDUC-14206";"";"120Ω";
"FD1";"FIDUCIALUFIDUCIAL";"FIDUCIALUFIDUCIAL";"FIDUCIAL-MICRO";"Fiducial Alignment Points";"";"";"";"";"";"";"";
"FD2";"FIDUCIALUFIDUCIAL";"FIDUCIALUFIDUCIAL";"FIDUCIAL-MICRO";"Fiducial Alignment Points";"";"";"";"";"";"";"";
"FD3";"FIDUCIALUFIDUCIAL";"FIDUCIALUFIDUCIAL";"FIDUCIAL-MICRO";"Fiducial Alignment Points";"";"";"";"";"";"";"";
"FD4";"FIDUCIALUFIDUCIAL";"FIDUCIALUFIDUCIAL";"FIDUCIAL-MICRO";"Fiducial Alignment Points";"";"";"";"";"";"";"";
"FRAME1";"FRAME-LEDGER";"FRAME-LEDGER";"CREATIVE_COMMONS";"Schematic Frame - Ledger";"";"";"";"";"";"";"";
"GEO";"JUMPER-SMT_2_NC_TRACE_SILK";"JUMPER-SMT_2_NC_TRACE_SILK";"SMT-JUMPER_2_NC_TRACE_SILK";"Normally closed trace jumper";"";"";"";"";"";"";"";
"H2";"STAND-OFFTIGHT";"STAND-OFFTIGHT";"STAND-OFF-TIGHT";"Stand Off";"";"";"";"";"";"";"";
"I2C";"JUMPER-SMT_3_2-NC_TRACE_SILK";"JUMPER-SMT_3_2-NC_TRACE_SILK";"SMT-JUMPER_3_2-NC_TRACE_SILK";"Normally closed trace jumper (2 of 2 connections)";"";"";"";"";"";"";"";
"J2";"";"USB_C_2-LAYER_PADS";"USB-C-16P-2LAYER-PADS";"USB Type C 16Pin Connector";"";"";"";"";"CONN-14122";"";"";
"J3";"QWIIC_RIGHT_ANGLE";"QWIIC_CONNECTORJS-1MM";"JST04_1MM_RA";"SparkFun I2C Standard Qwiic Connector";"";"";"";"";"CONN-13694";"";"QWIIC_RIGHT_ANGLE";
"J4";"QWIIC_RIGHT_ANGLE";"QWIIC_CONNECTORJS-1MM";"JST04_1MM_RA";"SparkFun I2C Standard Qwiic Connector";"";"";"";"";"CONN-13694";"";"QWIIC_RIGHT_ANGLE";
"J5";"";"CONN_111X11_NO_SILK";"1X11_NO_SILK";"Multi connection point. Often used as Generic Header-pin footprint for 0.1 inch spaced/style header connections";"";"";"";"";"";"";"";
"J6";"";"CONN_09NO_SILK";"1X09_NO_SILK";"Multi connection point. Often used as Generic Header-pin footprint for 0.1 inch spaced/style header connections";"";"";"";"";"";"";"";
"J7";"";"CONN_06NO_SILK_NO_POP";"1X06_NO_SILK";"Multi connection point. Often used as Generic Header-pin footprint for 0.1 inch spaced/style header connections";"";"";"";"";"";"";"";
"LOGO1";"OSHW-LOGOS";"OSHW-LOGOS";"OSHW-LOGO-S";"Open-Source Hardware (OSHW) Logo";"";"";"";"";"";"";"";
"LOGO2";"QWIIC_LOGO_4MM";"QWIIC_LOGO_4MM";"QWIIC_4MM";"Qwiic Logos for placement on schematic and PCB. The 5.5mm silk logo is best for placing next to Qwiic connector.";"";"";"";"";"";"";"";
"LOGO3";"SFE_LOGO_NAME_FLAME.2_INCH";"SFE_LOGO_NAME_FLAME.2_INCH";"SFE_LOGO_NAME_FLAME_.2";"SparkFun Font Logo w/ Flame";"";"";"";"";"";"";"";
"PPS";"JUMPER-SMT_2_NC_TRACE_SILK";"JUMPER-SMT_2_NC_TRACE_SILK";"SMT-JUMPER_2_NC_TRACE_SILK";"Normally closed trace jumper";"";"";"";"";"";"";"";
"PWR";"JUMPER-SMT_2_NC_TRACE_SILK";"JUMPER-SMT_2_NC_TRACE_SILK";"SMT-JUMPER_2_NC_TRACE_SILK";"Normally closed trace jumper";"";"";"";"";"";"";"";
"R1";"3.3k";"3.3KOHM-0603-1/10W-1%";"0603";"3.3kΩ resistor";"";"";"";"";"RES-07851";"";"3.3k";
"R2";"3.3k";"3.3KOHM-0603-1/10W-1%";"0603";"3.3kΩ resistor";"";"";"";"";"RES-07851";"";"3.3k";
"R3";"100K";"100KOHM-0402-1/16W-1%";"0402";"100kΩ resistor";"";"";"";"";"RES-13495";"";"100K";
"R4";"910";"910OHM-0603-1/10W-5%";"0603";"910 Ohm Resistor";"";"";"";"";"RES-13860";"";"910";
"R5";"470";"470OHM-0603-1/10W-1%";"0603";"470Ω resistor";"";"";"";"";"RES-07869";"";"470";
"R6";"470";"470OHM-0603-1/10W-1%";"0603";"470Ω resistor";"";"";"";"";"RES-07869";"";"470";
"R7";"910";"910OHM-0603-1/10W-5%";"0603";"910 Ohm Resistor";"";"";"";"";"RES-13860";"";"910";
"R8";"33";"33OHM_RA-1206-1/16W-5%";"1206_RA";"EXB-38V330JV";"";"";"";"";"RES-15081";"";"33";
"R9";"33";"33OHM_RA-1206-1/16W-5%";"1206_RA";"EXB-38V330JV";"";"";"";"";"RES-15081";"";"33";
"R10";"33";"33OHM_RA-1206-1/16W-5%";"1206_RA";"EXB-38V330JV";"";"";"";"";"RES-15081";"";"33";
"R11";"33";"33OHM_RA-1206-1/16W-5%";"1206_RA";"EXB-38V330JV";"";"";"";"";"RES-15081";"";"33";
"R12";"33";"33OHM-0603-1/10W-1%";"0603";"33Ω resistor";"";"";"";"";"RES-08270";"";"33";
"R13";"33";"33OHM-0603-1/10W-1%";"0603";"33Ω resistor";"";"";"";"";"RES-08270";"";"33";
"R14";"5.1k";"5.1KOHM-0402-1/16W-1%";"0402";"";"";"";"";"";"RES-14340";"";"5.1k";
"R15";"5.1k";"5.1KOHM-0402-1/16W-1%";"0402";"";"";"";"";"";"RES-14340";"";"5.1k";
"R16";"4.7k";"4.7KOHM-0402T-1/16W-1%";"0402-TIGHT";"4.7kΩ resistor";"";"";"";"";"RES-15343";"";"4.7k";
"R17";"1KOHM-0402-1/16W-1%";"1KOHM-0402-1/16W-1%";"0402";"1kΩ resistor";"";"";"";"";"RES-14342";"";"";
"R18";"1KOHM-0402-1/16W-1%";"1KOHM-0402-1/16W-1%";"0402";"1kΩ resistor";"";"";"";"";"RES-14342";"";"";
"R19";"1KOHM-0402-1/16W-1%";"1KOHM-0402-1/16W-1%";"0402";"1kΩ resistor";"";"";"";"";"RES-14342";"";"";
"R20";"1KOHM-0402-1/16W-1%";"1KOHM-0402-1/16W-1%";"0402";"1kΩ resistor";"";"";"";"";"RES-14342";"";"";
"R21";"27";"27OHM-0603-1/10W-1%";"0603";"27Ω resistor";"";"";"";"";"RES-09334";"";"27";
"R22";"27";"27OHM-0603-1/10W-1%";"0603";"27Ω resistor";"";"";"";"";"RES-09334";"";"27";
"R23";"4.7k";"4.7KOHM-0402T-1/16W-1%";"0402-TIGHT";"4.7kΩ resistor";"";"";"";"";"RES-15343";"";"4.7k";
"R24";"3.3k";"3.3KOHM-0603-1/10W-1%";"0603";"3.3kΩ resistor";"";"";"";"";"RES-07851";"";"3.3k";
"RTK";"JUMPER-SMT_2_NC_TRACE_SILK";"JUMPER-SMT_2_NC_TRACE_SILK";"SMT-JUMPER_2_NC_TRACE_SILK";"Normally closed trace jumper";"";"";"";"";"";"";"";
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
